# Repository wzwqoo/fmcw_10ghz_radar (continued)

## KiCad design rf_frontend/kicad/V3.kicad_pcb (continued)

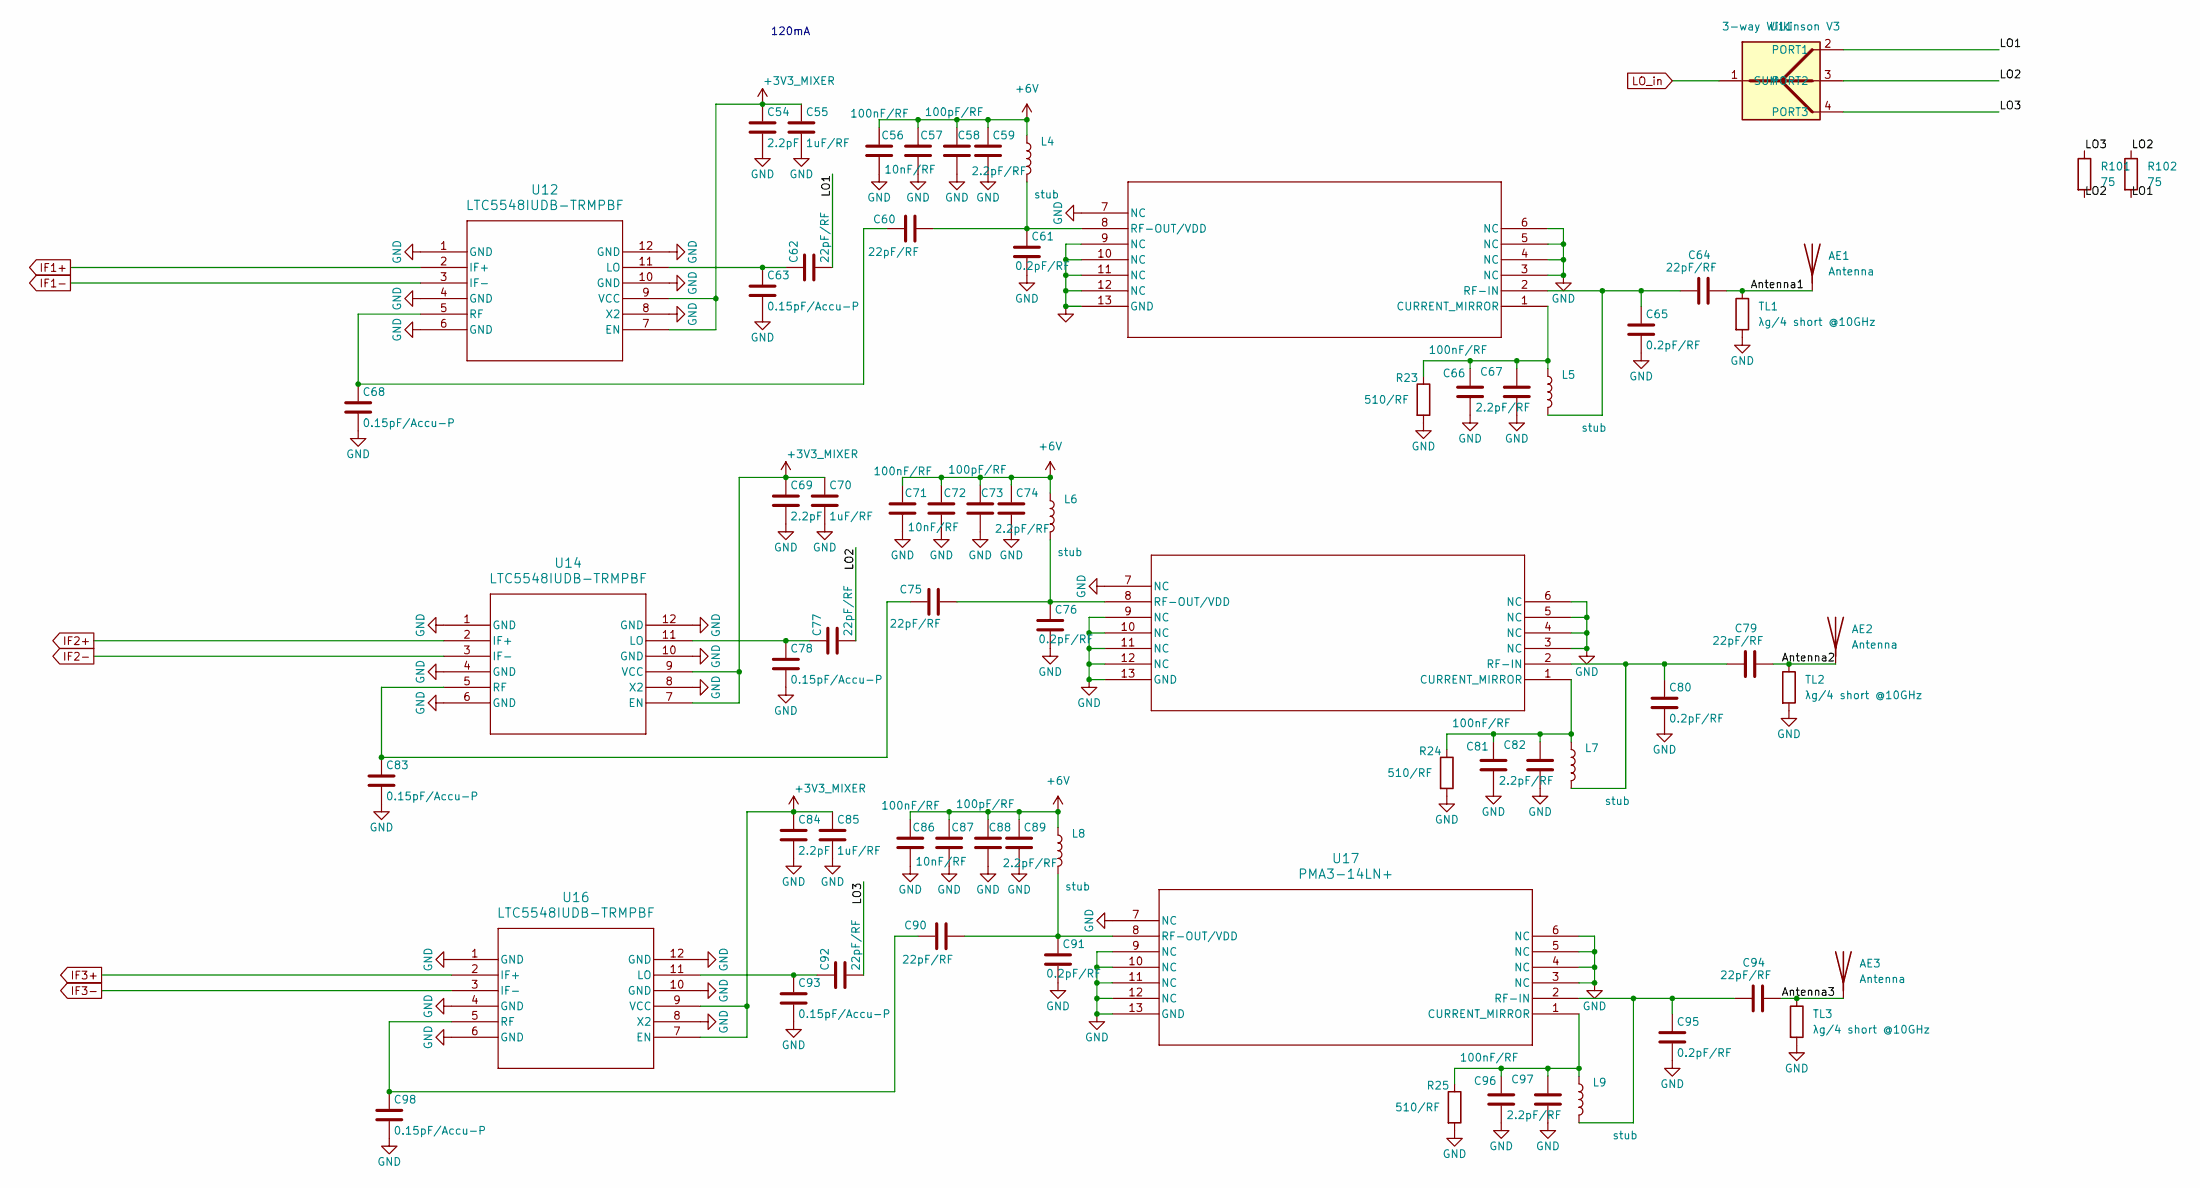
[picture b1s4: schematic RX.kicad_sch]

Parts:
AE1, AE2, AE3: Antenna; antenna_v3
C54, C69, C84: 2.2pF; C_0201_0603Metric
C55, C70, C85: 1uF/RF; C_0402_1005Metric
C56, C66, C71, C81, C86, C96: 100nF/RF; C_0402_1005Metric
C57, C72, C87: 10nF/RF; C_0402_1005Metric
C58, C73, C88: 100pF/RF; C_0402_1005Metric
C59, C67, C74, C82, C89, C97: 2.2pF/RF; C_0402_1005Metric
C60, C62, C64, C75, C77, C79, C90, C92, C94: 22pF/RF; C_0201_0603Metric
C61, C65, C76, C80, C91, C95: 0.2pF/RF; C_0201_0603Metric
C63, C68, C78, C83, C93, C98: 0.15pF/Accu-P; C_0201_0603Metric
L4, L5, L6, L7, L8, L9: stub; NetTie-2_SMD_Pad0.5mm
R23, R24, R25: 510/RF; R_0402_1005Metric
R101, R102: 75; R_0402_1005Metric
TL1, TL2, TL3: λg/4 short @10GHz; NetTie-2_SMD_Pad0.5mm
U11: 3-way Wilkinson V3; wilkinson3_v3
U12, U14, U16: LTC5548IUDB-TRMPBF; QFN-12-1EP_3x3mm_P0.5mm_EP1.45x1.45mm
U13, U15, U17: PMA3-14LN+; VQFN-12-1EP_4x4mm_P0.8mm_EP2.1x2.1mm; Part# PMA3-14LN+

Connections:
+3V3_MIXER: C54.1, C55.1, C69.1, C70.1, C84.1, C85.1, U12.7 (EN), U12.9 (VCC), U14.7 (EN), U14.9 (VCC), U16.7 (EN), U16.9 (VCC); also elsewhere on the board
+6V: C56.1, C57.1, C58.1, C59.1, C71.1, C72.1, C73.1, C74.1, C86.1, C87.1, C88.1, C89.1, L4.1, L6.1, L8.1; also elsewhere on the board
/RX/Antenna1: AE1.1, C64.2, TL1.1
/RX/Antenna2: AE2.1, C79.2, TL2.1
/RX/Antenna3: AE3.1, C94.2, TL3.1
/RX/LO1: C62.2, R102.2, U11.2 (PORT1)
/RX/LO2: C77.2, R101.2, R102.1, U11.3 (PORT2)
/RX/LO3: C92.2, R101.1, U11.4 (PORT3)
GND: C54.2, C55.2, C56.2, C57.2, C58.2, C59.2, C61.2, C63.2, C65.2, C66.2, C67.2, C68.2, C69.2, C70.2, C71.2, C72.2, C73.2, C74.2, C76.2, C78.2, C80.2, C81.2, C82.2, C83.2, C84.2, C85.2, C86.2, C87.2, C88.2, C89.2, C91.2, C93.2, C95.2, C96.2, C97.2, C98.2, R23.2, R24.2, R25.2, TL1.2, TL2.2, TL3.2, U12.1 (GND), U12.4 (GND), U12.6 (GND), U12.8 (X2), U12.10 (GND), U12.12 (GND), U12.13 (EP), U13.3 (NC), U13.4 (NC), U13.5 (NC), U13.6 (NC), U13.7 (NC), U13.9 (NC), U13.10 (NC), U13.11 (NC), U13.12 (NC), U13.13 (GND), U14.1 (GND), U14.4 (GND), U14.6 (GND), U14.8 (X2), U14.10 (GND), U14.12 (GND), U14.13 (EP), U15.3 (NC), U15.4 (NC), U15.5 (NC), U15.6 (NC), U15.7 (NC), U15.9 (NC), U15.10 (NC), U15.11 (NC), U15.12 (NC), U15.13 (GND), U16.1 (GND), U16.4 (GND), U16.6 (GND), U16.8 (X2), U16.10 (GND), U16.12 (GND), U16.13 (EP), U17.3 (NC), U17.4 (NC), U17.5 (NC), U17.6 (NC), U17.7 (NC), U17.9 (NC), U17.10 (NC), U17.11 (NC), U17.12 (NC), U17.13 (GND); also elsewhere on the board
IF1+: U12.2 (IF+); also elsewhere on the board
IF1-: U12.3 (IF-); also elsewhere on the board
IF2+: U14.2 (IF+); also elsewhere on the board
IF2-: U14.3 (IF-); also elsewhere on the board
IF3+: U16.2 (IF+); also elsewhere on the board
IF3-: U16.3 (IF-); also elsewhere on the board
LO_in: U11.1 (SUM); also elsewhere on the board
unnamed: C62.1, C63.1, U12.11 (LO)
unnamed: C60.1, C68.1, U12.5 (RF)
unnamed: C66.1, C67.1, L5.1, R23.1, U13.1 (CURRENT_MIRROR)
unnamed: C64.1, C65.1, L5.2, U13.2 (RF-IN)
unnamed: C60.2, C61.1, L4.2, U13.8 (RF-OUT/VDD)
unnamed: C77.1, C78.1, U14.11 (LO)
unnamed: C75.1, C83.1, U14.5 (RF)
unnamed: C81.1, C82.1, L7.1, R24.1, U15.1 (CURRENT_MIRROR)
unnamed: C79.1, C80.1, L7.2, U15.2 (RF-IN)
unnamed: C75.2, C76.1, L6.2, U15.8 (RF-OUT/VDD)
unnamed: C92.1, C93.1, U16.11 (LO)
unnamed: C90.1, C98.1, U16.5 (RF)
unnamed: C96.1, C97.1, L9.1, R25.1, U17.1 (CURRENT_MIRROR)
unnamed: C94.1, C95.1, L9.2, U17.2 (RF-IN)
unnamed: C90.2, C91.1, L8.2, U17.8 (RF-OUT/VDD)

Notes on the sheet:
120mA

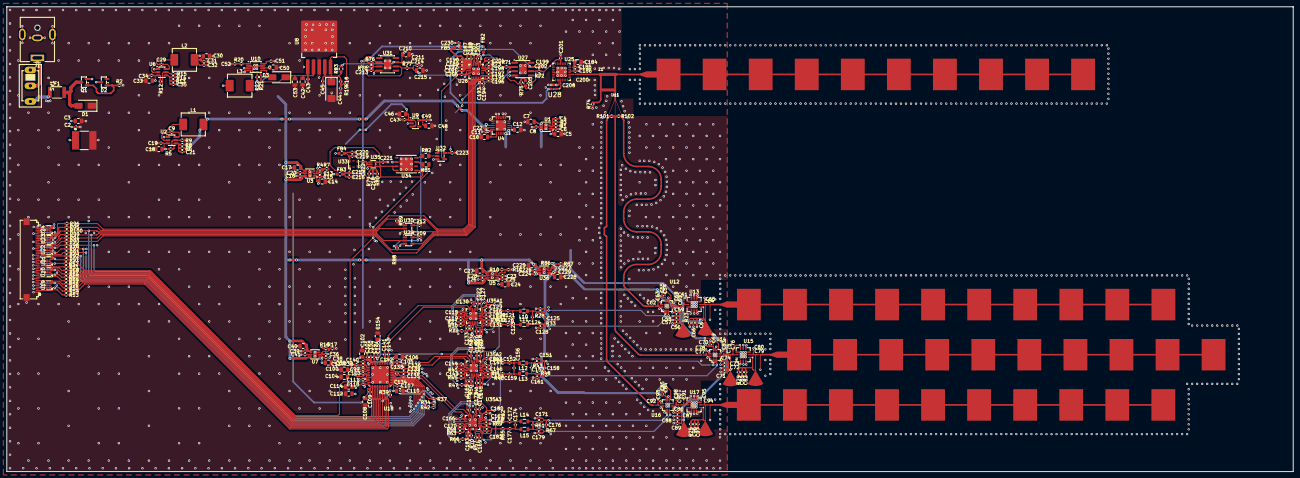
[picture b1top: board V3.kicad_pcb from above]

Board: 4 copper layers, 384.3 x 138.8 mm, 404 parts (0 on the bottom side), 222 nets.

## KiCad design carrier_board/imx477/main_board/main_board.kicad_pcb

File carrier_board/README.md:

# `carrier_board/` — camera + radar carrier

The carrier connects two OV9281 global-shutter cameras, the radar front-end,
and an I²S impact microphone to an Embedfire Artix-7 module. Captured data can
be buffered and offloaded to the host over Gigabit Ethernet.

## `ov9281/` — OV9281 carrier

| Sheet or file | Interface |
|---|---|
| `extension.kicad_sch` (CAM) | Two OV9281 modules, 200 mm apart. Each MC20901 bridge converts two-lane MIPI D-PHY high-speed signals to LVDS and carries low-power signals separately. |
| `FPGA.kicad_sch` | Two 140-pin board-to-board connectors to the Artix-7 module, JTAG, and the I²S microphone interface. |
| `FMCW.kicad_sch` | 40-pin shielded FPC to the radar front-end. |
| `ETH.kicad_sch` | RTL8211F-CG Gigabit Ethernet PHY and HY911130A RJ45 with integrated magnetics. |
| `power.kicad_sch` | 12 V barrel input, TPS54302 bucks, and TLV755 LDOs. |
| `v2.kicad_pcb` | Routed 228 × 80 mm, six-layer carrier. |
| [`fpga_pins.xdc`](ov9281/fpga_pins.xdc) and [`fpga_pinmap.csv`](ov9281/fpga_pinmap.csv) | Carrier-to-module pin assignments for the XC7A100T/200T. |

The camera receptacles use placeholder footprints pending mating-fit verification.
Assembly and bring-up remain open.

## Opening the board

```sh
kicad carrier_board/ov9281/v2.kicad_pro   # KiCad 10
```

The IMX477 main board, sensor board, render and lens holder are in
[`archive/imx477/`](archive/imx477/).

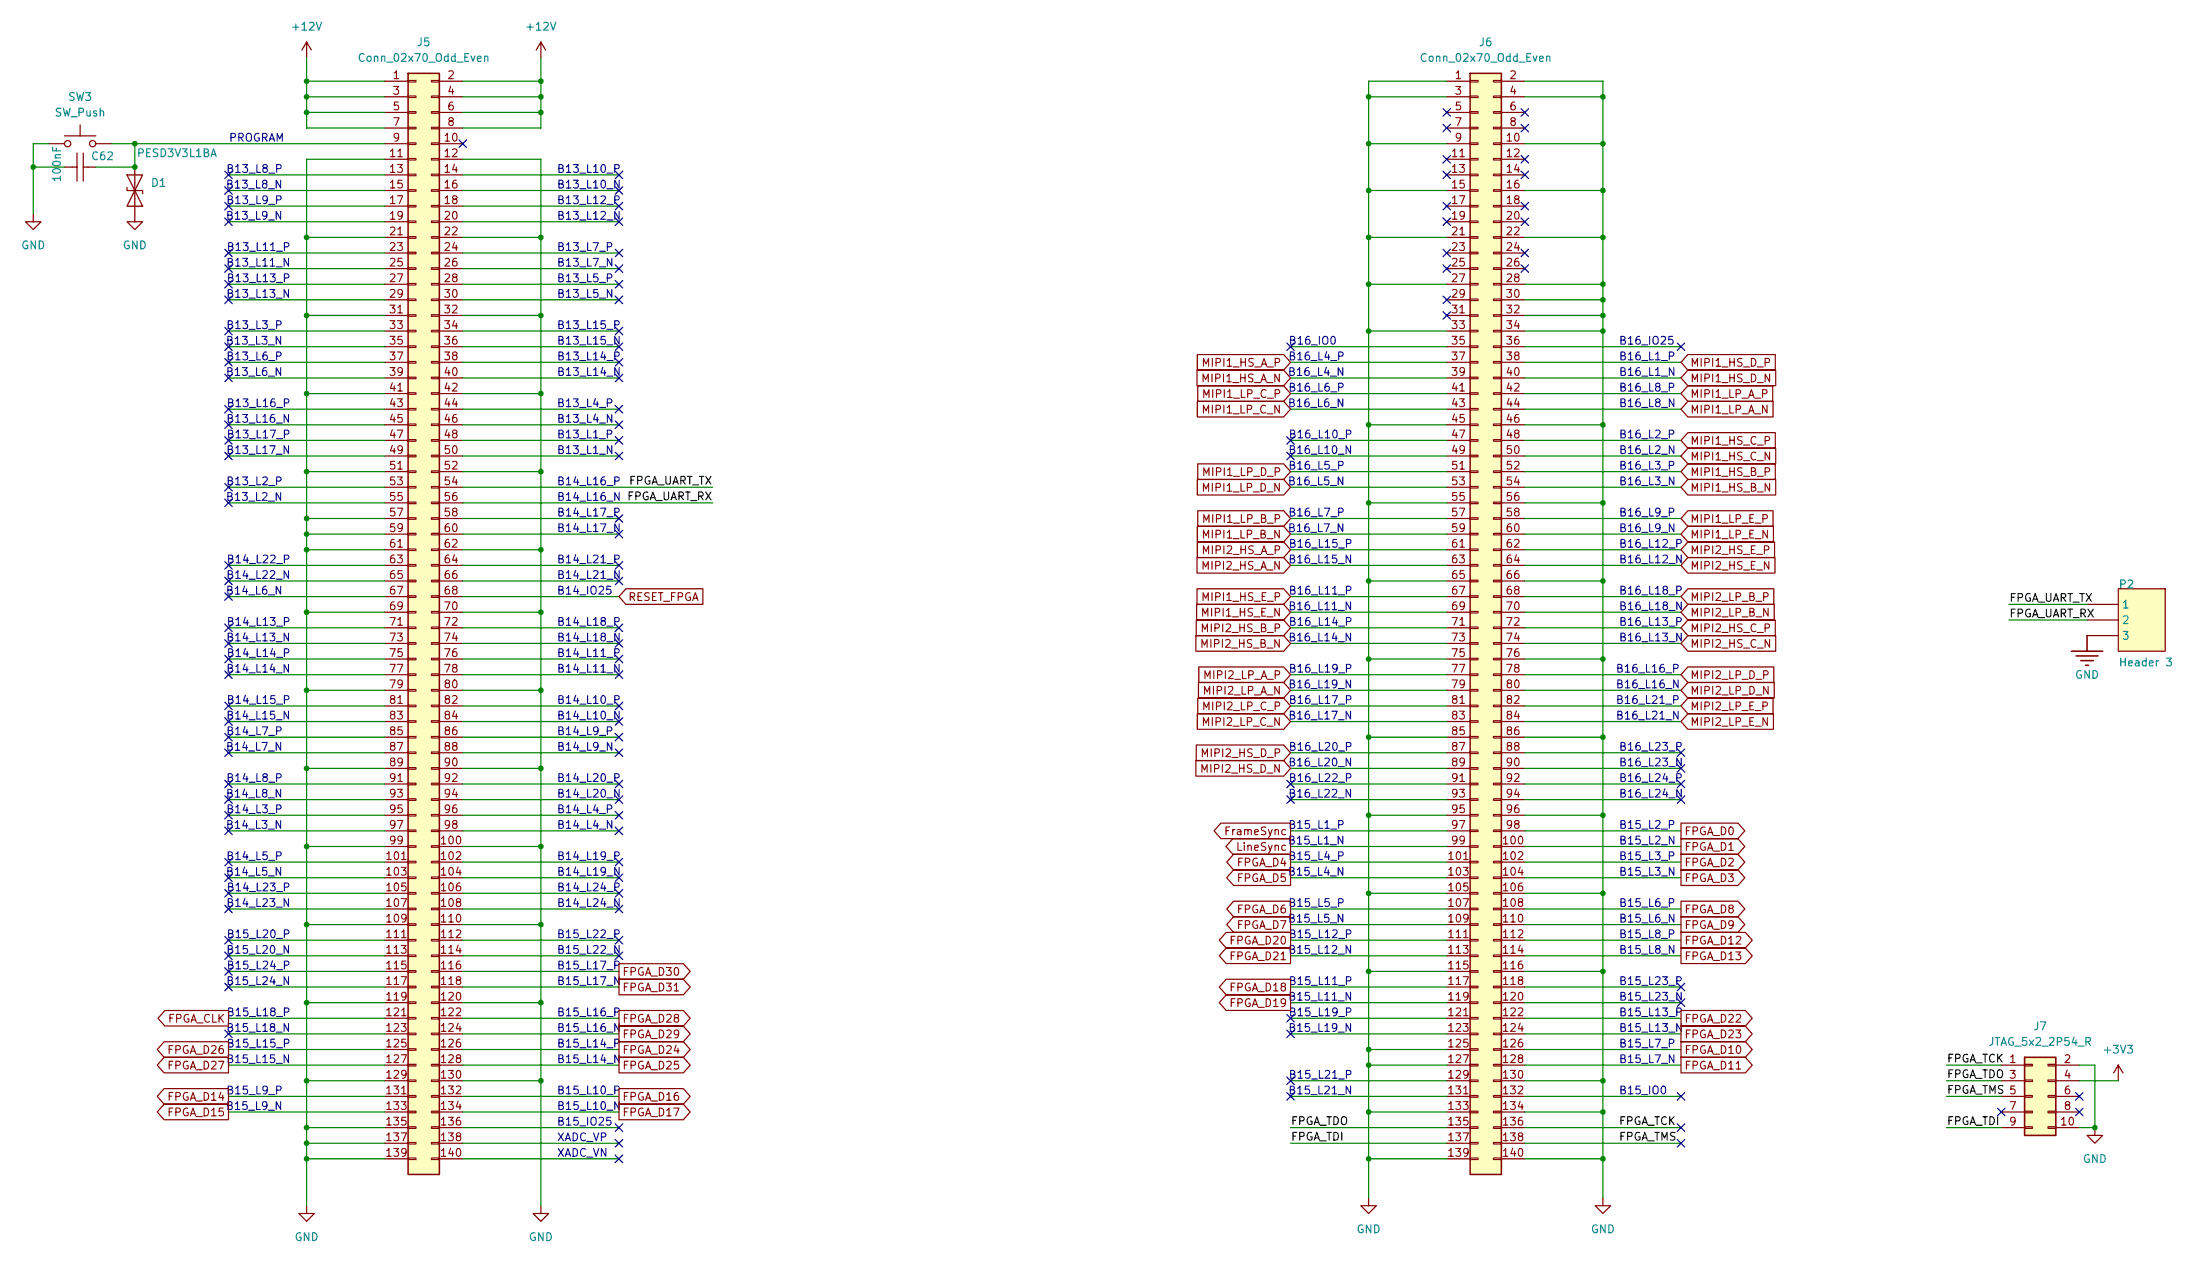
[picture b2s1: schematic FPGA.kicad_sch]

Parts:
C62: 100nF; C_0603_1608Metric; TOLERANCE ±10%; RATINGS 16V; X7R; MANUFACTURER PART NUMBE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 CC0402KRX7R7BB103
D1: PESD3V3L1BA; D_SOD-323
J5, J6: Conn_02x70_Odd_Even; CONN-SMD_140P-P0.50_B2BM-2X70-0P5_BZOOC
J7: JTAG_5x2_2P54_R; PinHeader_2x05_P2.54mm_Horizontal
P2: Header 3; PinHeader_1x03_P2.54mm_Vertical
SW3: SW_Push; SW_Push_1P1T_NO_CK_KMR2; Part# KMR242NGLFS; LCSC Part # C2804669

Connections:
+3V3: J7.4; also elsewhere on the board
+12V: J5.1, J5.2, J5.3, J5.4, J5.5, J5.6, J5.7, J5.8; also elsewhere on the board
/FPGA/FPGA_TCK: J6.136, J7.1
/FPGA/FPGA_TDI: J6.137, J7.9
/FPGA/FPGA_TDO: J6.135, J7.3
/FPGA/FPGA_TMS: J6.138, J7.5
/FPGA/FPGA_UART_RX: J5.56, P2.2
/FPGA/FPGA_UART_TX: J5.54, P2.1
FPGA_CLK: J5.121; also elsewhere on the board
FPGA_D0: J6.98; also elsewhere on the board
FPGA_D1: J6.100; also elsewhere on the board
FPGA_D2: J6.102; also elsewhere on the board
FPGA_D3: J6.104; also elsewhere on the board
FPGA_D4: J6.101; also elsewhere on the board
FPGA_D5: J6.103; also elsewhere on the board
FPGA_D6: J6.107; also elsewhere on the board
FPGA_D7: J6.109; also elsewhere on the board
FPGA_D8: J6.108; also elsewhere on the board
FPGA_D9: J6.110; also elsewhere on the board
FPGA_D10: J6.126; also elsewhere on the board
FPGA_D11: J6.128; also elsewhere on the board
FPGA_D12: J6.112; also elsewhere on the board
FPGA_D13: J6.114; also elsewhere on the board
FPGA_D14: J5.131; also elsewhere on the board
FPGA_D15: J5.133; also elsewhere on the board
FPGA_D16: J5.132; also elsewhere on the board
FPGA_D17: J5.134; also elsewhere on the board
FPGA_D18: J6.117; also elsewhere on the board
FPGA_D19: J6.119; also elsewhere on the board
FPGA_D20: J6.111; also elsewhere on the board
FPGA_D21: J6.113; also elsewhere on the board
FPGA_D22: J6.122; also elsewhere on the board
FPGA_D23: J6.124; also elsewhere on the board
FPGA_D24: J5.126; also elsewhere on the board
FPGA_D25: J5.128; also elsewhere on the board
FPGA_D26: J5.125; also elsewhere on the board
FPGA_D27: J5.127; also elsewhere on the board
FPGA_D28: J5.122; also elsewhere on the board
FPGA_D29: J5.124; also elsewhere on the board
FPGA_D30: J5.116; also elsewhere on the board
FPGA_D31: J5.118; also elsewhere on the board
FrameSync: J6.97; also elsewhere on the board
GND: C62.2, D1.1 (A1), J5.11, J5.12, J5.21, J5.22, J5.31, J5.32, J5.41, J5.42, J5.51, J5.52, J5.57, J5.59, J5.61, J5.62, J5.69, J5.70, J5.79, J5.80, J5.89, J5.90, J5.99, J5.100, J5.109, J5.110, J5.119, J5.120, J5.129, J5.130, J5.135, J5.137, J5.139, J6.1, J6.2, J6.3, J6.4, J6.9, J6.10, J6.15, J6.16, J6.21, J6.22, J6.27, J6.28, J6.30, J6.32, J6.33, J6.34, J6.45, J6.46, J6.55, J6.56, J6.65, J6.66, J6.75, J6.76, J6.85, J6.86, J6.95, J6.96, J6.105, J6.106, J6.115, J6.116, J6.125, J6.127, J6.130, J6.133, J6.134, J6.139, J6.140, J7.2, J7.10, P2.3, SW3.1; also elsewhere on the board
LineSync: J6.99; also elsewhere on the board
MIPI1_HS_A_N: J6.39; also elsewhere on the board
MIPI1_HS_A_P: J6.37; also elsewhere on the board
MIPI1_HS_B_N: J6.54; also elsewhere on the board
MIPI1_HS_B_P: J6.52; also elsewhere on the board
MIPI1_HS_C_N: J6.50; also elsewhere on the board
MIPI1_HS_C_P: J6.48; also elsewhere on the board
MIPI1_HS_D_N: J6.40; also elsewhere on the board
MIPI1_HS_D_P: J6.38; also elsewhere on the board
MIPI1_HS_E_N: J6.69; also elsewhere on the board
MIPI1_HS_E_P: J6.67; also elsewhere on the board
MIPI1_LP_A_N: J6.44; also elsewhere on the board
MIPI1_LP_A_P: J6.42; also elsewhere on the board
MIPI1_LP_B_N: J6.59; also elsewhere on the board
MIPI1_LP_B_P: J6.57; also elsewhere on the board
MIPI1_LP_C_N: J6.43; also elsewhere on the board
MIPI1_LP_C_P: J6.41; also elsewhere on the board
MIPI1_LP_D_N: J6.53; also elsewhere on the board
MIPI1_LP_D_P: J6.51; also elsewhere on the board
MIPI1_LP_E_N: J6.60; also elsewhere on the board
MIPI1_LP_E_P: J6.58; also elsewhere on the board
MIPI2_HS_A_N: J6.63; also elsewhere on the board
MIPI2_HS_A_P: J6.61; also elsewhere on the board
MIPI2_HS_B_N: J6.73; also elsewhere on the board
MIPI2_HS_B_P: J6.71; also elsewhere on the board
MIPI2_HS_C_N: J6.74; also elsewhere on the board
MIPI2_HS_C_P: J6.72; also elsewhere on the board
MIPI2_HS_D_N: J6.89; also elsewhere on the board
MIPI2_HS_D_P: J6.87; also elsewhere on the board
MIPI2_HS_E_N: J6.64; also elsewhere on the board
MIPI2_HS_E_P: J6.62; also elsewhere on the board
MIPI2_LP_A_N: J6.79; also elsewhere on the board
MIPI2_LP_A_P: J6.77; also elsewhere on the board
MIPI2_LP_B_N: J6.70; also elsewhere on the board
MIPI2_LP_B_P: J6.68; also elsewhere on the board
MIPI2_LP_C_N: J6.83; also elsewhere on the board
MIPI2_LP_C_P: J6.81; also elsewhere on the board
MIPI2_LP_D_N: J6.80; also elsewhere on the board
MIPI2_LP_D_P: J6.78; also elsewhere on the board
MIPI2_LP_E_N: J6.84; also elsewhere on the board
MIPI2_LP_E_P: J6.82; also elsewhere on the board
unnamed: C62.1, D1.2 (A2), J5.9, SW3.2
RESET_FPGA: J5.68; also elsewhere on the board

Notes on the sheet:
B16_L14_N
B14_L24_P
B14_L15_P
B16_L1_P
B14_L22_N
B15_L5_P
B16_L3_P
B16_L13_N
B15_L17_N
B13_L6_P
B16_L21_N
B14_L14_P
B15_L1_N
B13_L2_P
B15_L24_P
B15_L15_P
B14_IO25
B16_L20_P
B14_L18_P
B13_L13_N
B16_L24_N
B15_L7_P
B13_L16_N
B13_L13_P
B15_L11_N
B15_L21_N
B15_L22_P
B15_L20_P
B13_L1_P
B14_L9_P
B13_L4_P
B13_L14_N
B15_L14_P
B15_L24_N
B16_L11_P
B14_L3_P
B15_L8_N
B13_L8_N
B13_L14_P
B15_L23_P

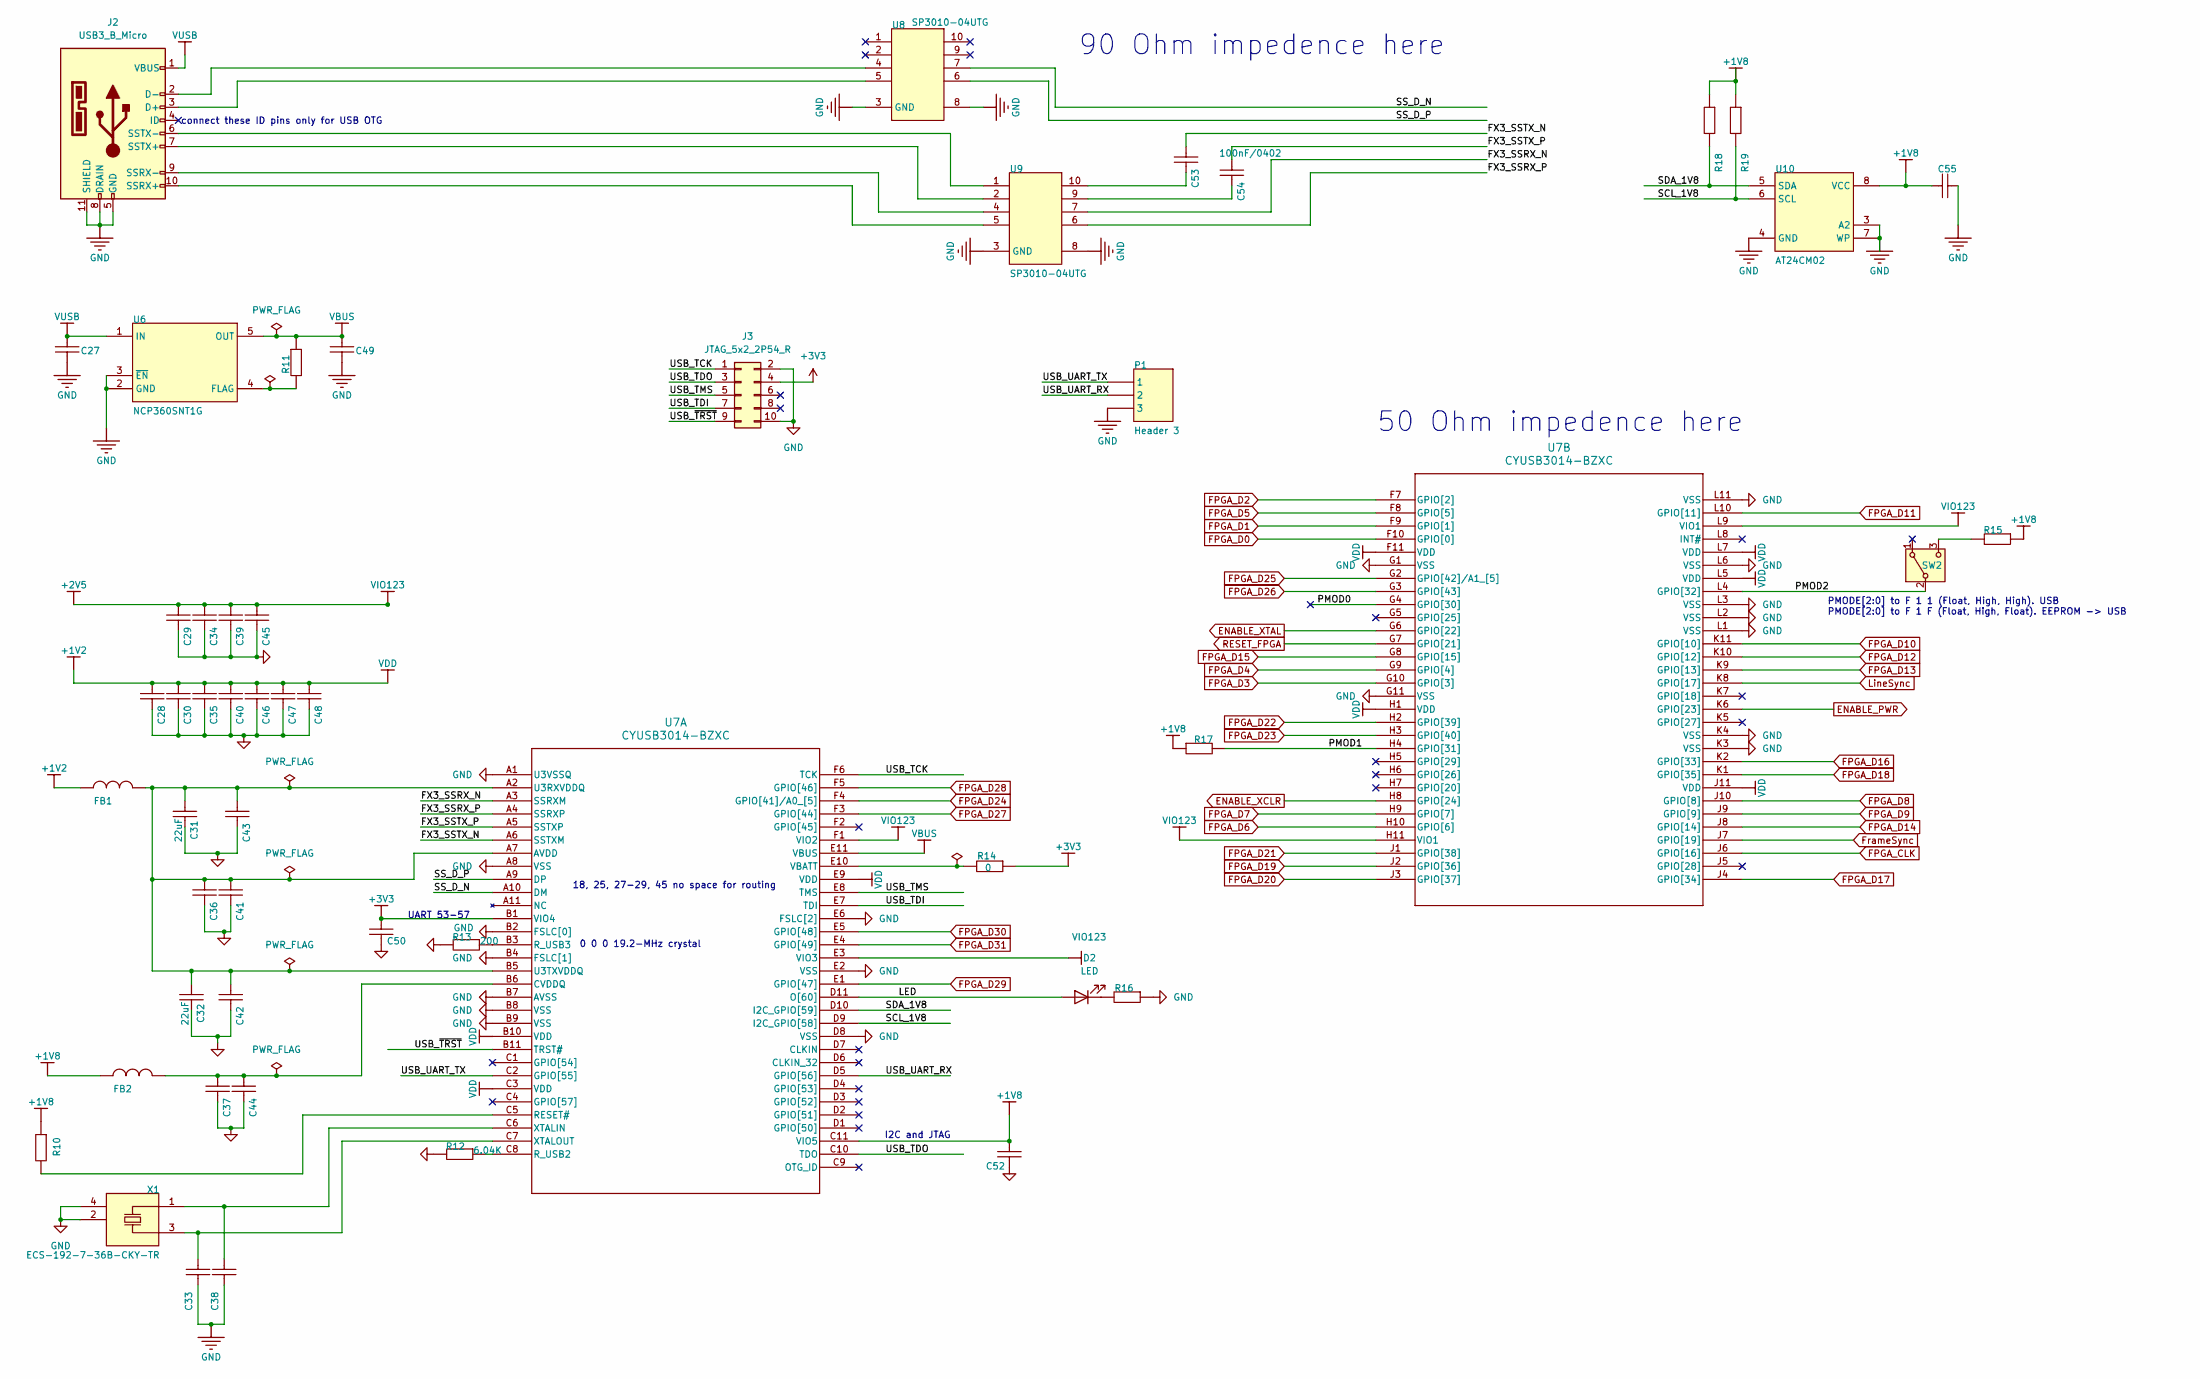
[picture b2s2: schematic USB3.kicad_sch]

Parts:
C27, C49: 10uF; C_0603_1608Metric; TOLERANCE ±20%; RATINGS 50V; X5R; MANUFACTURER PART NUMBE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 UMK325BJ106MM-T
C28, C29, C30, C33, C34, C35, C36, C37, C38, C39, C40, C42, C43, C44, C45, C46, C47, C48, C50, C52, C55: 100nF; C_0603_1608Metric; TOLERANCE ±10%; RATINGS 16V; X7R; MANUFACTURER PART NUMBE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 CC0402KRX7R7BB103
C31, C32: 22uF; C_0603_1608Metric; RATINGS 50V; NP0; MANUFACTURER PART NUMBE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 06035A561JAT2A
C41: 2.2uF; C_0603_1608Metric; TOLERANCE ±10%; RATINGS 16V; X7R; MANUFACTURER PART NUMBE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 CC0402KRX7R7BB103
C53, C54: 100nF/0402; C_0402_1005Metric; TOLERANCE ±10%; RATINGS 16V; X7R; MANUFACTURER PART NUMBE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 CC0402KRX7R7BB103
D2: LED; LED_0603_1608Metric
FB1, FB2: 100Ω at 100 MHz; L_0805_2012Metric; Part# MPZ2012S101ATD25; LCSC Part # C307776
J2: USB3_B_Micro; USB3_Micro-B_Connfly_DS1104-01
J3: JTAG_5x2_2P54_R; PinHeader_2x05_P2.54mm_Horizontal
P1: Header 3; PinHeader_1x03_P2.54mm_Vertical
R10, R11, R15, R16, R17, R18, R19: 3.3K; R_0603_1608Metric; RATINGS 1/16 W; TOLERANCE ±5%; MANUFACTURER PART NUMBE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 RC0402JR-073K3L
R12: 6.04K; R_0603_1608Metric; RATINGS 1/16 W; TOLERANCE ±5%; MANUFACTURER PART NUMBE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 RC0402JR-073K3L
R13: 200; R_0603_1608Metric; RATINGS 1/16 W; TOLERANCE ±5%; MANUFACTURER PART NUMBE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 RC0402JR-073K3L
R14: 0; R_0603_1608Metric; RATINGS 1/16 W; TOLERANCE ±5%; MANUFACTURER PART NUMBE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 RC0402JR-073K3L
SW2: SW_SPDT; SW_SPDT_CK_JS102011SAQN; Part# JS102011SAQN; LCSC Part # C221660
U6: NCP360SNT1G; TSOP5_3X1P5_ONS; Part# NCP360SNT1G; LCSC Part # C603707
U7: CYUSB3014-BZXC; PG-TFBGA-121-800_INF
U8, U9: SP3010-04UTG; Diodes_UDFN-10_1.0x2.5mm_P0.5mm; Part# SP3010-04UTG; LCSC Part # C126837
U10: AT24CM02; SOIC-8-1EP_3.9x4.9mm_P1.27mm_EP2.29x3mm; Part# AT24CM02-SSHM-T; LCSC Part # C779670
X1: ECS-192-7-36B-CKY-TR; Oscillator_SMD_ECS_2520MV-xxx-xx-4Pin_2.5x2.0mm; Part# ECS ECS-192-7-36B-CKY-TR; LCSC Part # C2450510

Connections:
+1V2: C28.2, C30.2, C35.2, C40.2, C46.2, C47.2, C48.2, FB1.1, U7.B10 (VDD), U7.C3 (VDD), U7.E9 (VDD), U7.F11 (VDD), U7.H1 (VDD), U7.J11 (VDD), U7.L5 (VDD), U7.L7 (VDD); also elsewhere on the board
+1V8: C52.2, C55.2, FB2.1, R10.1, R15.2, R17.2, R18.1, R19.1, U7.C11 (VIO5), U10.8 (VCC); also elsewhere on the board
+2V5: C29.2, C34.2, C39.2, C45.2, U7.E3 (VIO3), U7.F1 (VIO2), U7.H11 (VIO1), U7.L9 (VIO1); also elsewhere on the board
+3V3: C50.2, J3.4, R14.2, U7.B1 (VIO4); also elsewhere on the board
/USB3/FX3_SSRX_N: U7.A3 (SSRXM), U9.7
/USB3/FX3_SSRX_P: U7.A4 (SSRXP), U9.6
/USB3/FX3_SSTX_N: C53.2, U7.A6 (SSTXM)
/USB3/FX3_SSTX_P: C54.2, U7.A5 (SSTXP)
/USB3/LED: D2.2 (A), U7.D11 (O[60])
/USB3/PMOD0: U7.G4 (GPIO[30])
/USB3/PMOD1: R17.1, U7.H4 (GPIO[31])
/USB3/PMOD2: SW2.2 (B), U7.L4 (GPIO[32])
/USB3/SCL_1V8: R19.2, U7.D9 (I2C_GPIO[58]), U10.6 (SCL)
/USB3/SDA_1V8: R18.2, U7.D10 (I2C_GPIO[59]), U10.5 (SDA)
/USB3/SS_D_N: U7.A10 (DM), U8.7
/USB3/SS_D_P: U7.A9 (DP), U8.6
/USB3/USB_TCK: J3.1, U7.F6 (TCK)
/USB3/USB_TDI: J3.7, U7.E7 (TDI)
/USB3/USB_TDO: J3.3, U7.C10 (TDO)
/USB3/USB_TMS: J3.5, U7.E8 (TMS)
/USB3/USB_UART_RX: P1.2, U7.D5 (GPIO[56])
/USB3/USB_UART_TX: P1.1, U7.C2 (GPIO[55])
/USB3/USB_~TRST: J3.9, U7.B11 (TRST#)
ENABLE_PWR: U7.K6 (GPIO[23]); also elsewhere on the board
ENABLE_XCLR: U7.H8 (GPIO[24]); also elsewhere on the board
ENABLE_XTAL: U7.G6 (GPIO[22]); also elsewhere on the board
FPGA_CLK: U7.J6 (GPIO[16]); also elsewhere on the board
FPGA_D0: U7.F10 (GPIO[0]); also elsewhere on the board
FPGA_D1: U7.F9 (GPIO[1]); also elsewhere on the board
FPGA_D2: U7.F7 (GPIO[2]); also elsewhere on the board
FPGA_D3: U7.G10 (GPIO[3]); also elsewhere on the board
FPGA_D4: U7.G9 (GPIO[4]); also elsewhere on the board
FPGA_D5: U7.F8 (GPIO[5]); also elsewhere on the board
FPGA_D6: U7.H10 (GPIO[6]); also elsewhere on the board
FPGA_D7: U7.H9 (GPIO[7]); also elsewhere on the board
FPGA_D8: U7.J10 (GPIO[8]); also elsewhere on the board
FPGA_D9: U7.J9 (GPIO[9]); also elsewhere on the board
FPGA_D10: U7.K11 (GPIO[10]); also elsewhere on the board
FPGA_D11: U7.L10 (GPIO[11]); also elsewhere on the board
FPGA_D12: U7.K10 (GPIO[12]); also elsewhere on the board
FPGA_D13: U7.K9 (GPIO[13]); also elsewhere on the board
FPGA_D14: U7.J8 (GPIO[14]); also elsewhere on the board
FPGA_D15: U7.G8 (GPIO[15]); also elsewhere on the board
FPGA_D16: U7.K2 (GPIO[33]); also elsewhere on the board
FPGA_D17: U7.J4 (GPIO[34]); also elsewhere on the board
FPGA_D18: U7.K1 (GPIO[35]); also elsewhere on the board
FPGA_D19: U7.J2 (GPIO[36]); also elsewhere on the board
FPGA_D20: U7.J3 (GPIO[37]); also elsewhere on the board
FPGA_D21: U7.J1 (GPIO[38]); also elsewhere on the board
FPGA_D22: U7.H2 (GPIO[39]); also elsewhere on the board
FPGA_D23: U7.H3 (GPIO[40]); also elsewhere on the board
FPGA_D24: U7.F4 (GPIO[41]/A0_[5]); also elsewhere on the board
FPGA_D25: U7.G2 (GPIO[42]/A1_[5]); also elsewhere on the board
FPGA_D26: U7.G3 (GPIO[43]); also elsewhere on the board
FPGA_D27: U7.F3 (GPIO[44]); also elsewhere on the board
FPGA_D28: U7.F5 (GPIO[46]); also elsewhere on the board
FPGA_D29: U7.E1 (GPIO[47]); also elsewhere on the board
FPGA_D30: U7.E5 (GPIO[48]); also elsewhere on the board
FPGA_D31: U7.E4 (GPIO[49]); also elsewhere on the board
FrameSync: U7.J7 (GPIO[19]); also elsewhere on the board
GND: C27.2, C28.1, C29.1, C30.1, C31.2, C32.2, C33.2, C34.1, C35.1, C36.1, C37.1, C38.2, C39.1, C40.1, C41.1, C42.1, C43.1, C44.1, C45.1, C46.1, C47.1, C48.1, C49.2, C50.1, C52.1, C55.1, J2.5 (GND), J2.8 (DRAIN), J2.11 (SHIELD), J3.2, J3.10, P1.3, R12.1, R13.1, R16.2, U6.2 (GND), U6.3 (~EN), U7.A1 (U3VSSQ), U7.A8 (VSS), U7.B2 (FSLC[0]), U7.B4 (FSLC[1]), U7.B7 (AVSS), U7.B8 (VSS), U7.B9 (VSS), U7.D8 (VSS), U7.E2 (VSS), U7.E6 (FSLC[2]), U7.G1 (VSS), U7.G11 (VSS), U7.K3 (VSS), U7.K4 (VSS), U7.L1 (VSS), U7.L2 (VSS), U7.L3 (VSS), U7.L6 (VSS), U7.L11 (VSS), U8.3 (GND), U8.8 (GND), U9.3 (GND), U9.8 (GND), U10.3 (A2), U10.4 (GND), U10.7 (WP), X1.2 (NC), X1.4 (NC); also elsewhere on the board
LineSync: U7.K8 (GPIO[17]); also elsewhere on the board
unnamed: C53.1, U9.10
unnamed: C54.1, U9.9
unnamed: D2.1 (K), R16.1
unnamed: J2.3 (D+), U8.5
unnamed: J2.2 (D-), U8.4
unnamed: J2.10 (SSRX+), U9.5
unnamed: J2.9 (SSRX-), U9.4
unnamed: J2.7 (SSTX+), U9.2
unnamed: J2.6 (SSTX-), U9.1
unnamed: R15.1, SW2.3 (C)
unnamed: R11.1, U6.4 (FLAG)
unnamed: C31.1, C32.1, C36.2, C41.2, C42.2, C43.2, FB1.2, U7.A2 (U3RXVDDQ), U7.A7 (AVDD), U7.B5 (U3TXVDDQ)
unnamed: C37.2, C44.2, FB2.2, U7.B6 (CVDDQ)
unnamed: R10.2, U7.C5 (RESET#)
unnamed: R12.2, U7.C8 (R_USB2)
unnamed: R13.2, U7.B3 (R_USB3)
unnamed: R14.1, U7.E10 (VBATT)
unnamed: C38.1, U7.C6 (XTALIN), X1.1 (X1)
unnamed: C33.1, U7.C7 (XTALOUT), X1.3 (X2)
RESET_FPGA: U7.G7 (GPIO[21]); also elsewhere on the board
VBUS: C49.1, R11.2, U6.5 (OUT), U7.E11 (VBUS)
VUSB: C27.1, J2.1 (VBUS), U6.1 (IN)

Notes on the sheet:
0 0 0 19.2-MHz crystal
UART 53-57
connect these ID pins only for USB OTG
I2C and JTAG
18, 25, 27-29, 45 no space for routing
90 Ohm impedence here
PMODE[2:0] to F 1 1 (Float, High, High). USB PMODE[2:0] to F 1 F (Float, High, Float). EEPROM -> USB
50 Ohm impedence here

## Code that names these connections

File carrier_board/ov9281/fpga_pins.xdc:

# Generated by scripts/make_xdc.py from fpga_pinmap.csv (CameraShield V2 carrier, Embedfire XC7A100T/200T core board B1). Do not edit by hand.

set_property -dict {PACKAGE_PIN L13 IOSTANDARD LVCMOS33} [get_ports adar_cs_n]  ;# J4.111 B15_L20_P
set_property -dict {PACKAGE_PIN L15 IOSTANDARD LVCMOS33} [get_ports adar_fault_n]  ;# J4.112 B15_L22_P
set_property -dict {PACKAGE_PIN L16 IOSTANDARD LVCMOS33} [get_ports adar_reset_n]  ;# J4.114 B15_L22_N
set_property -dict {PACKAGE_PIN N19 IOSTANDARD LVCMOS33} [get_ports adc_d0]  ;# J4.116 B15_L17_P
set_property -dict {PACKAGE_PIN M16 IOSTANDARD LVCMOS33} [get_ports adc_d1]  ;# J4.115 B15_L24_P
set_property -dict {PACKAGE_PIN N20 IOSTANDARD LVCMOS33} [get_ports adc_d2]  ;# J4.118 B15_L17_N
set_property -dict {PACKAGE_PIN M17 IOSTANDARD LVCMOS33} [get_ports adc_d3]  ;# J4.117 B15_L24_N
set_property -dict {PACKAGE_PIN L18 IOSTANDARD LVCMOS33} [get_ports adc_d4]  ;# J4.122 B15_L16_P
set_property -dict {PACKAGE_PIN M20 IOSTANDARD LVCMOS33} [get_ports adc_d5]  ;# J4.121 B15_L18_P
set_property -dict {PACKAGE_PIN N18 IOSTANDARD LVCMOS33} [get_ports adc_d6]  ;# J4.124 B15_L16_N
set_property -dict {PACKAGE_PIN K13 IOSTANDARD LVCMOS33} [get_ports adc_d7]  ;# J4.123 B15_L18_N
set_property -dict {PACKAGE_PIN R18 IOSTANDARD LVCMOS33} [get_ports adf_ce_3v3]  ;# J4.104 B14_L19_N
set_property -dict {PACKAGE_PIN N14 IOSTANDARD LVCMOS33} [get_ports adf_le_3v3]  ;# J4.105 B14_L23_P
set_property -dict {PACKAGE_PIN N15 IOSTANDARD LVCMOS33} [get_ports adf_muxout_3v3]  ;# J4.108 B14_L24_N
set_property -dict {PACKAGE_PIN R19 IOSTANDARD LVCMOS33} [get_ports adf_txdata_3v3]  ;# J4.101 B14_L5_P
# CAM0_HS_CLK_P/CAM0_HS_CLK_N: J4.18/J4.20 B13_L12_P/B13_L12_N
set_property -dict {PACKAGE_PIN W12 IOSTANDARD LVDS_25 DIFF_TERM FALSE} [get_ports cam0_hs_clk_p]
set_property -dict {PACKAGE_PIN V13 IOSTANDARD LVDS_25 DIFF_TERM FALSE} [get_ports cam0_hs_clk_n]
# CAM0_HS_D0_P/CAM0_HS_D0_N: J4.14/J4.16 B13_L10_P/B13_L10_N
set_property -dict {PACKAGE_PIN W10 IOSTANDARD LVDS_25 DIFF_TERM FALSE} [get_ports cam0_hs_d0_p]
set_property -dict {PACKAGE_PIN Y11 IOSTANDARD LVDS_25 DIFF_TERM FALSE} [get_ports cam0_hs_d0_n]
# CAM0_HS_D1_P/CAM0_HS_D1_N: J4.24/J4.26 B13_L7_P/B13_L7_N
set_property -dict {PACKAGE_PIN AB12 IOSTANDARD LVDS_25 DIFF_TERM FALSE} [get_ports cam0_hs_d1_p]
set_property -dict {PACKAGE_PIN AA9 IOSTANDARD LVDS_25 DIFF_TERM FALSE} [get_ports cam0_hs_d1_n]
set_property -dict {PACKAGE_PIN V10 IOSTANDARD LVCMOS33} [get_ports cam0_lp_clk_n]  ;# J4.19 B13_L9_N
set_property -dict {PACKAGE_PIN AA11 IOSTANDARD LVCMOS33} [get_ports cam0_lp_clk_p]  ;# J4.17 B13_L9_P
set_property -dict {PACKAGE_PIN AA10 IOSTANDARD LVCMOS33} [get_ports cam0_lp_d0_n]  ;# J4.15 B13_L8_N
set_property -dict {PACKAGE_PIN AB10 IOSTANDARD LVCMOS33} [get_ports cam0_lp_d0_p]  ;# J4.13 B13_L8_P
set_property -dict {PACKAGE_PIN W11 IOSTANDARD LVCMOS33} [get_ports cam0_lp_d1_n]  ;# J4.25 B13_L11_N
set_property -dict {PACKAGE_PIN Y12 IOSTANDARD LVCMOS33} [get_ports cam0_lp_d1_p]  ;# J4.23 B13_L11_P
# CAM1_HS_CLK_P/CAM1_HS_CLK_N: J5.67/J5.69 B16_L11_P/B16_L11_N
set_property -dict {PACKAGE_PIN B18 IOSTANDARD LVDS_25 DIFF_TERM FALSE} [get_ports cam1_hs_clk_p]
set_property -dict {PACKAGE_PIN D17 IOSTANDARD LVDS_25 DIFF_TERM FALSE} [get_ports cam1_hs_clk_n]
# CAM1_HS_D0_P/CAM1_HS_D0_N: J5.71/J5.73 B16_L14_P/B16_L14_N
set_property -dict {PACKAGE_PIN D19 IOSTANDARD LVDS_25 DIFF_TERM FALSE} [get_ports cam1_hs_d0_p]
set_property -dict {PACKAGE_PIN F18 IOSTANDARD LVDS_25 DIFF_TERM FALSE} [get_ports cam1_hs_d0_n]
# CAM1_HS_D1_P/CAM1_HS_D1_N: J5.61/J5.63 B16_L15_P/B16_L15_N
set_property -dict {PACKAGE_PIN E18 IOSTANDARD LVDS_25 DIFF_TERM FALSE} [get_ports cam1_hs_d1_p]
set_property -dict {PACKAGE_PIN B20 IOSTANDARD LVDS_25 DIFF_TERM FALSE} [get_ports cam1_hs_d1_n]
set_property -dict {PACKAGE_PIN C18 IOSTANDARD LVCMOS33} [get_ports cam1_lp_clk_n]  ;# J5.64 B16_L12_N
set_property -dict {PACKAGE_PIN C17 IOSTANDARD LVCMOS33} [get_ports cam1_lp_clk_p]  ;# J5.62 B16_L12_P
set_property -dict {PACKAGE_PIN D20 IOSTANDARD LVCMOS33} [get_ports cam1_lp_d0_n]  ;# J5.70 B16_L18_N
set_property -dict {PACKAGE_PIN F20 IOSTANDARD LVCMOS33} [get_ports cam1_lp_d0_p]  ;# J5.68 B16_L18_P
set_property -dict {PACKAGE_PIN A13 IOSTANDARD LVCMOS33} [get_ports cam1_lp_d1_n]  ;# J5.60 B16_L9_N
set_property -dict {PACKAGE_PIN A16 IOSTANDARD LVCMOS33} [get_ports cam1_lp_d1_p]  ;# J5.58 B16_L9_P
set_property -dict {PACKAGE_PIN AB21 IOSTANDARD LVCMOS33} [get_ports eth_intb]  ;# J4.88 B14_L9_N
set_property -dict {PACKAGE_PIN W22 IOSTANDARD LVCMOS33} [get_ports eth_mdc]  ;# J4.85 B14_L7_P
set_property -dict {PACKAGE_PIN AA20 IOSTANDARD LVCMOS33} [get_ports eth_mdio]  ;# J4.87 B14_L7_N
set_property -dict {PACKAGE_PIN Y22 IOSTANDARD LVCMOS33} [get_ports eth_nrst]  ;# J4.86 B14_L9_P
set_property -dict {PACKAGE_PIN V19 IOSTANDARD LVCMOS33} [get_ports eth_rxd0]  ;# J4.75 B14_L14_P
set_property -dict {PACKAGE_PIN AA19 IOSTANDARD LVCMOS33} [get_ports eth_rxd1]  ;# J4.77 B14_L14_N
set_property -dict {PACKAGE_PIN AB20 IOSTANDARD LVCMOS33} [get_ports eth_rxd2]  ;# J4.81 B14_L15_P
set_property -dict {PACKAGE_PIN V17 IOSTANDARD LVCMOS33} [get_ports eth_rxd3]  ;# J4.83 B14_L15_N
set_property -dict {PACKAGE_PIN Y19 IOSTANDARD LVCMOS33} [get_ports eth_rx_clk]  ;# J4.71 B14_L13_P
set_property -dict {PACKAGE_PIN V18 IOSTANDARD LVCMOS33} [get_ports eth_rx_ctl]  ;# J4.73 B14_L13_N
set_property -dict {PACKAGE_PIN V20 IOSTANDARD LVCMOS33} [get_ports eth_txd0]  ;# J4.76 B14_L11_P
set_property -dict {PACKAGE_PIN W19 IOSTANDARD LVCMOS33} [get_ports eth_txd1]  ;# J4.78 B14_L11_N
set_property -dict {PACKAGE_PIN AB22 IOSTANDARD LVCMOS33} [get_ports eth_txd2]  ;# J4.82 B14_L10_P
set_property -dict {PACKAGE_PIN U20 IOSTANDARD LVCMOS33} [get_ports eth_txd3]  ;# J4.84 B14_L10_N
set_property -dict {PACKAGE_PIN U18 IOSTANDARD LVCMOS33} [get_ports eth_tx_clk]  ;# J4.72 B14_L18_P
set_property -dict {PACKAGE_PIN P14 IOSTANDARD LVCMOS33} [get_ports eth_tx_ctl]  ;# J4.74 B14_L18_N
set_property -dict {PACKAGE_PIN P16 IOSTANDARD LVCMOS33} [get_ports spi_miso_3v3]  ;# J4.107 B14_L23_N
set_property -dict {PACKAGE_PIN R17 IOSTANDARD LVCMOS33} [get_ports spi_mosi_3v3]  ;# J4.106 B14_L24_P
set_property -dict {PACKAGE_PIN T19 IOSTANDARD LVCMOS33} [get_ports spi_sclk_3v3]  ;# J4.103 B14_L5_N
set_property -dict {PACKAGE_PIN M22 IOSTANDARD LVCMOS33} [get_ports conv_start]  ;# J4.125 B15_L15_P
set_property -dict {PACKAGE_PIN K17 IOSTANDARD LVCMOS33} [get_ports data_ready]  ;# J4.113 B15_L20_N
set_property -dict {PACKAGE_PIN AA18 IOSTANDARD LVCMOS33} [get_ports fpga_uart_rx]  ;# J4.56 B14_L16_N
set_property -dict {PACKAGE_PIN W17 IOSTANDARD LVCMOS33} [get_ports fpga_uart_tx]  ;# J4.54 B14_L16_P
set_property -dict {PACKAGE_PIN AA15 IOSTANDARD LVCMOS33} [get_ports reset]  ;# J4.35 B13_L3_N
set_property -dict {PACKAGE_PIN E22 IOSTANDARD LVCMOS33} [get_ports sck_bclk]  ;# J5.84 B16_L21_N
set_property -dict {PACKAGE_PIN L20 IOSTANDARD LVCMOS33} [get_ports sclk_adc]  ;# J4.126 B15_L14_P
set_property -dict {PACKAGE_PIN C20 IOSTANDARD LVCMOS33} [get_ports scl_3v3]  ;# J5.77 B16_L19_P
set_property -dict {PACKAGE_PIN A21 IOSTANDARD LVCMOS33} [get_ports sd]  ;# J5.82 B16_L21_P
set_property -dict {PACKAGE_PIN C22 IOSTANDARD LVCMOS33} [get_ports sda_3v3]  ;# J5.79 B16_L19_N
set_property -dict {PACKAGE_PIN B22 IOSTANDARD LVCMOS33} [get_ports ws_lrclk]  ;# J5.87 B16_L20_P
set_property -dict {PACKAGE_PIN A18 IOSTANDARD LVCMOS33} [get_ports fsync_3v3]  ;# J5.80 B16_L16_N
set_property -dict {PACKAGE_PIN A20 IOSTANDARD LVCMOS33} [get_ports xshutdown_3v3]  ;# J5.78 B16_L16_P
set_property -dict {PACKAGE_PIN R14 IOSTANDARD LVCMOS33} [get_ports spare1_3v3]  ;# J4.102 B14_L19_P
set_property -dict {PACKAGE_PIN T21 IOSTANDARD LVCMOS33} [get_ports spare2_3v3]  ;# J4.97 B14_L3_N
set_property -dict {PACKAGE_PIN P19 IOSTANDARD LVCMOS33} [get_ports spare3_3v3]  ;# J4.98 B14_L4_N

# Fix attempt 2026-11-11: consistent RGMII output buffer, evaluated across silicon corners.
# Pin/IOSTANDARD constraints above are unchanged. Complete PHY timing/STA is still required.
set_property -dict {DRIVE 8 SLEW FAST} [get_ports eth_txd0]
set_property -dict {DRIVE 8 SLEW FAST} [get_ports eth_txd1]
set_property -dict {DRIVE 8 SLEW FAST} [get_ports eth_txd2]
set_property -dict {DRIVE 8 SLEW FAST} [get_ports eth_txd3]
set_property -dict {DRIVE 8 SLEW FAST} [get_ports eth_tx_clk]
set_property -dict {DRIVE 8 SLEW FAST} [get_ports eth_tx_ctl]
